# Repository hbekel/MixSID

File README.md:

# MixSID
*flexible Stereo-SID-board with integrated channel mixer*

The MixSID is a stereo SID board for the C64 that can be used with any combination 
of SID models on a wide range of C64 mainboards.

Features include an integrated stereo channel mixer, 
pragmatic stereo addressing scheme, flexible handling of io areas,
onboard audio input, output and digiboost circuits, 
dedicated stereo output, full paddle compatibility and versatile digital control.

For more information, please see the project page, available in both 
[english](http://www.henning-bekel.de/mixsid) and [german](http://www.henning-bekel.de/mixsid/de).

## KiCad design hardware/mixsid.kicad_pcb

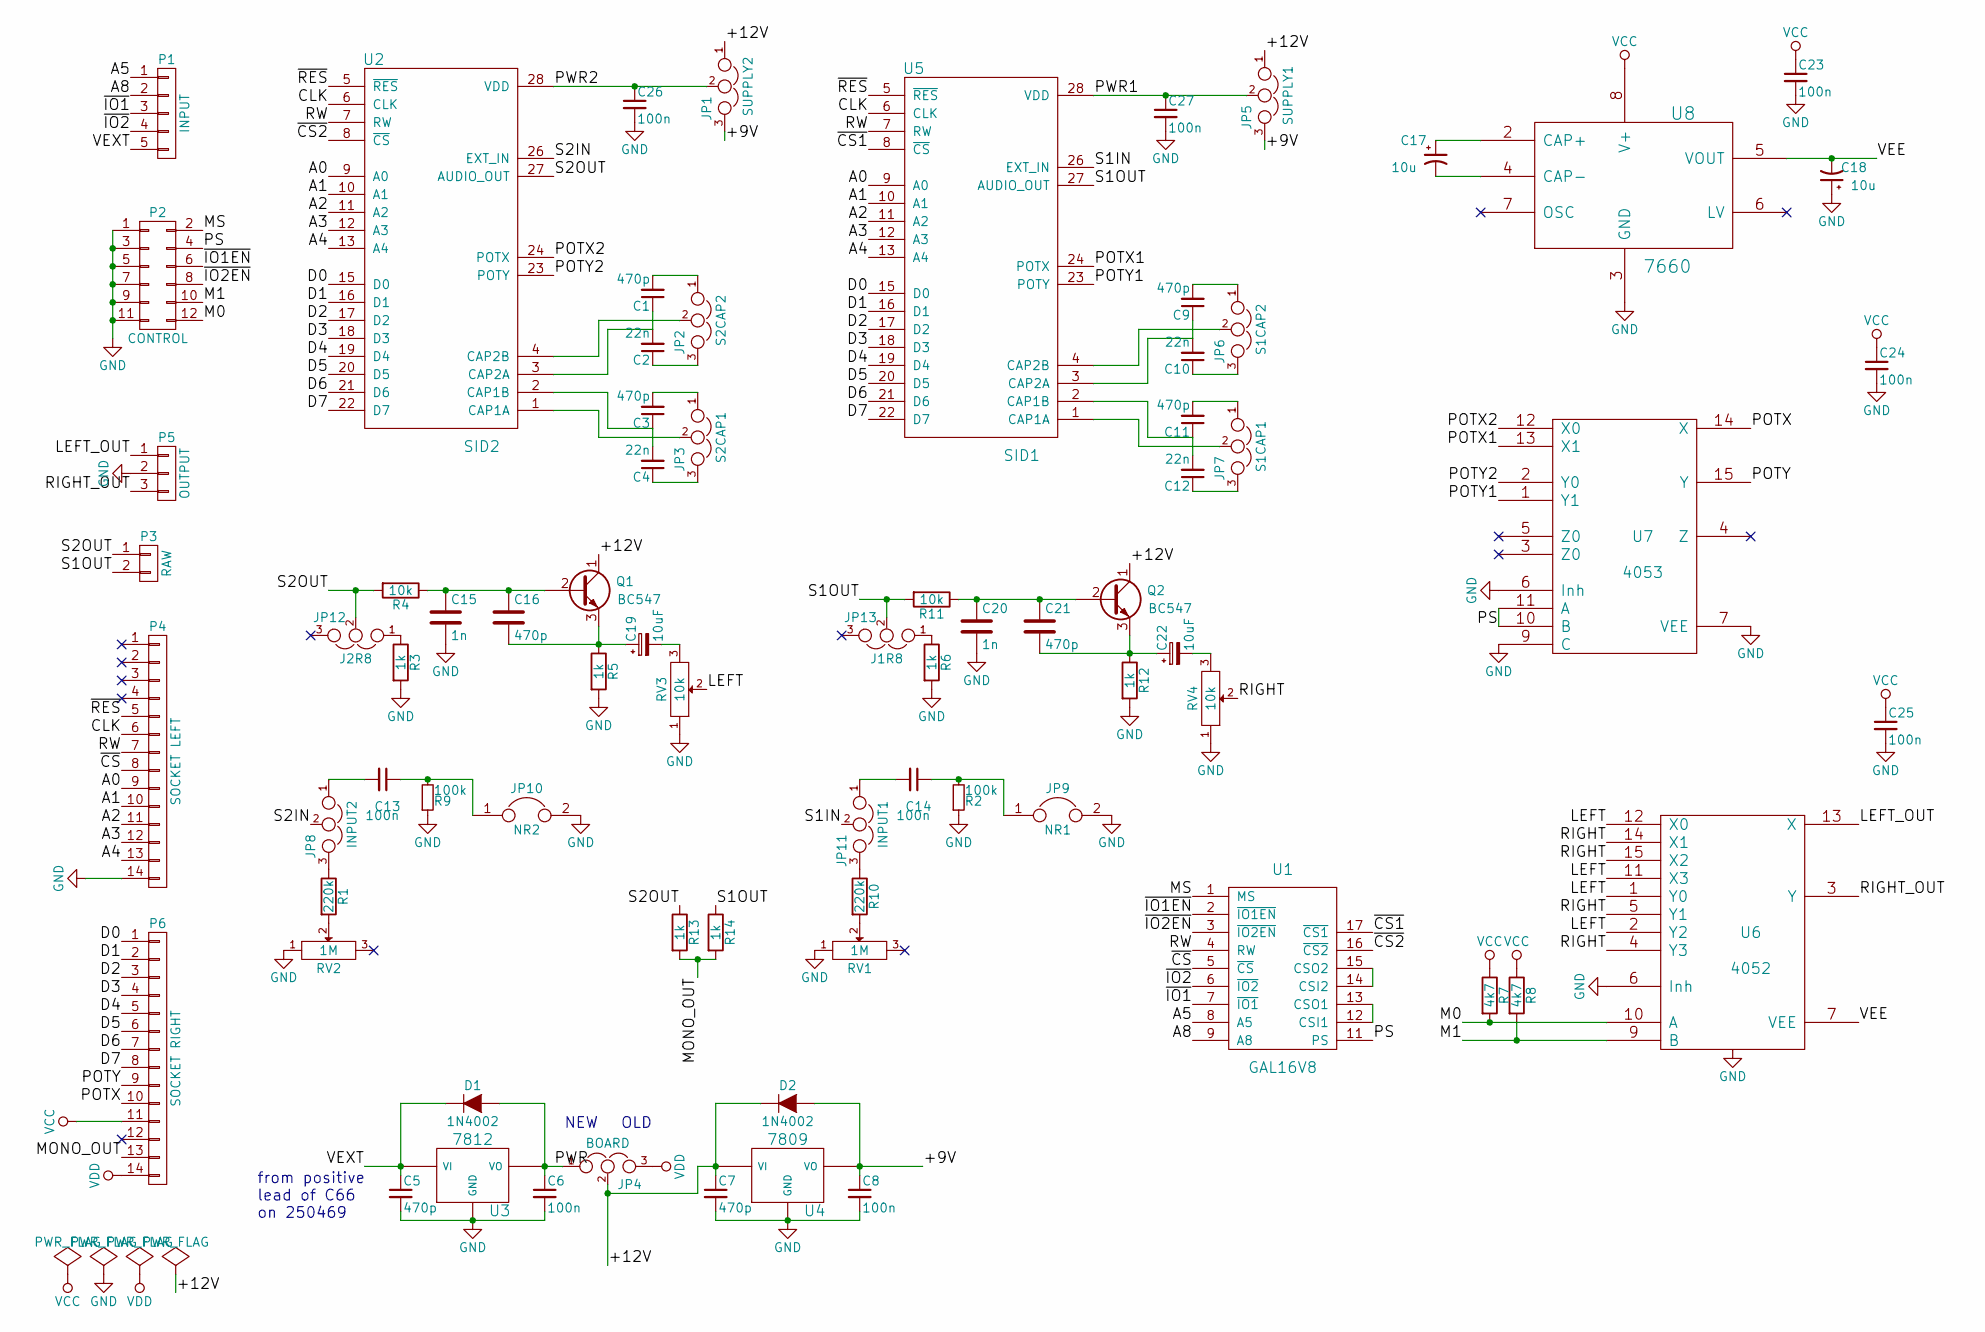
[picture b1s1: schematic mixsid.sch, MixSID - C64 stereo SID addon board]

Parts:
C1, C3, C5, C7, C9, C11, C16, C21: 470p; C_Disc_D3_P2.5
C2, C4, C10, C12: 22n; C_Disc_D3_P2.5
C6, C8, C13, C14, C23, C24, C25, C26, C27: 100n; C_Disc_D3_P2.5
C15, C20: 1n; C_Disc_D3_P2.5
C17, C18: 10u; C_Radial_D5_L6_P2.5
C19, C22: 10uF; C_Radial_D5_L6_P2.5
D1, D2: 1N4002; DO-41
JP1: SUPPLY2; Pin_Header_Straight_1x03_Pitch2.00mm
JP2: S2CAP2; Pin_Header_Straight_1x03_Pitch2.00mm
JP3: S2CAP1; Pin_Header_Straight_1x03_Pitch2.00mm
JP4: BOARD; Pin_Header_Straight_1x03
JP5: SUPPLY1; Pin_Header_Straight_1x03_Pitch2.00mm
JP6: S1CAP2; Pin_Header_Straight_1x03_Pitch2.00mm
JP7: S1CAP1; Pin_Header_Straight_1x03_Pitch2.00mm
JP8: INPUT2; Pin_Header_Straight_1x03_Pitch2.00mm
JP9: NR1; Pin_Header_Straight_1x02
JP10: NR2; Pin_Header_Straight_1x02
JP11: INPUT1; Pin_Header_Straight_1x03_Pitch2.00mm
JP12: J2R8; Pin_Header_Straight_1x03_Pitch2.00mm
JP13: J1R8; Pin_Header_Straight_1x03_Pitch2.00mm
P1: INPUT; Pin_Header_Straight_1x05
P2: CONTROL; Pin_Header_Straight_2x06
P3: RAW; Pin_Header_Straight_1x02
P4: SOCKET LEFT; Pin_Header_Straight_1x14
P5: OUTPUT; Pin_Header_Straight_1x03
P6: SOCKET RIGHT; Pin_Header_Straight_1x14
Q1, Q2: BC547; TO-92_Inline_Narrow_Oval
R1, R10: 220k; R1
R2, R9: 100k; R1
R3, R5, R6, R12, R13, R14: 1k; R1
R4, R11: 10k; R1
R7, R8: 4k7; R1
RV1, RV2: 1M; Potentiometer_Bourns_3296W_3-8Zoll_Inline_ScrewUp
RV3, RV4: 10k; Potentiometer_Bourns_3339P_Angular_ScrewUp
U1: GAL16V8; DIP-20_W7.62mm
U2: SID2; DIP-28_W15.24mm
U3: 7812; TO-220
U4: 7809; TO-220
U5: SID1; DIP-28_W15.24mm
U6: 4052; DIP-16_W7.62mm
U7: 4053; DIP-16_W7.62mm
U8: 7660; DIP-8_W7.62mm

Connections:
/+9V: C8.1, D2.2 (A), JP1.3, JP5.3, U4.3 (VO)
/+12V: C7.1, D2.1 (K), JP1.1, JP4.2, JP5.1, Q1.1 (C), Q2.1 (C), U4.1 (VI)
/A0: P4.9, U2.9 (A0), U5.9 (A0)
/A1: P4.10, U2.10 (A1), U5.10 (A1)
/A2: P4.11, U2.11 (A2), U5.11 (A2)
/A3: P4.12, U2.12 (A3), U5.12 (A3)
/A4: P4.13, U2.13 (A4), U5.13 (A4)
/A5: P1.1, U1.8 (A5)
/A8: P1.2, U1.9 (A8)
/CLK: P4.6, U2.6 (CLK), U5.6 (CLK)
/D0: P6.1, U2.15 (D0), U5.15 (D0)
/D1: P6.2, U2.16 (D1), U5.16 (D1)
/D2: P6.3, U2.17 (D2), U5.17 (D2)
/D3: P6.4, U2.18 (D3), U5.18 (D3)
/D4: P6.5, U2.19 (D4), U5.19 (D4)
/D5: P6.6, U2.20 (D5), U5.20 (D5)
/D6: P6.7, U2.21 (D6), U5.21 (D6)
/D7: P6.8, U2.22 (D7), U5.22 (D7)
/LEFT: RV3.2, U6.1 (Y0), U6.2 (Y2), U6.11 (X3), U6.12 (X0)
/LEFT_OUT: P5.1, U6.13 (X)
/M0: P2.12, R7.2, U6.10 (A)
/M1: P2.10, R8.2, U6.9 (B)
/MONO_OUT: P6.13, R13.2, R14.2
/MS: P2.2, U1.1 (MS)
/POTX: P6.10, U7.14 (X)
/POTX1: U5.24 (POTX), U7.13 (X1)
/POTX2: U2.24 (POTX), U7.12 (X0)
/POTY: P6.9, U7.15 (Y)
/POTY1: U5.23 (POTY), U7.1 (Y1)
/POTY2: U2.23 (POTY), U7.2 (Y0)
/PS: P2.4, U1.11 (PS), U7.10 (B), U7.11 (A)
/PWR: C6.1, D1.2 (A), JP4.1, U3.3 (VO)
/PWR1: C27.1, JP5.2, U5.28 (VDD)
/PWR2: C26.1, JP1.2, U2.28 (VDD)
/RIGHT: RV4.2, U6.4 (Y3), U6.5 (Y1), U6.14 (X1), U6.15 (X2)
/RIGHT_OUT: P5.3, U6.3 (Y)
/RW: P4.7, U1.4 (RW), U2.7 (RW), U5.7 (RW)
/S1IN: JP11.2, U5.26 (EXT_IN)
/S1OUT: JP13.2, P3.2, R11.2, R14.1, U5.27 (AUDIO_OUT)
/S2IN: JP8.2, U2.26 (EXT_IN)
/S2OUT: JP12.2, P3.1, R4.2, R13.1, U2.27 (AUDIO_OUT)
/VEE: C18.2, U6.7 (VEE), U8.5 (VOUT)
/VEXT: C5.1, D1.1 (K), P1.5, U3.1 (VI)
/~CS: P4.8, U1.5 (~CS)
/~CS1: U1.17 (~CS1), U5.8 (~CS)
/~CS2: U1.16 (~CS2), U2.8 (~CS)
/~IO1: P1.3, U1.7 (~IO1)
/~IO1EN: P2.6, U1.2 (~IO1EN)
/~IO2: P1.4, U1.6 (~IO2)
/~IO2EN: P2.8, U1.3 (~IO2EN)
/~RES: P4.5, U2.5 (~RES), U5.5 (~RES)
GND: C5.2, C6.2, C7.2, C8.2, C15.2, C18.1, C20.2, C23.2, C24.2, C25.2, C26.2, C27.2, JP9.2, JP10.2, P2.1, P2.3, P2.5, P2.7, P2.9, P2.11, P4.14, P5.2, R2.1, R3.2, R5.2, R6.2, R9.1, R12.2, RV1.1, RV2.1, RV3.1, RV4.1, U1.10 (GND), U2.14 (GND), U3.2 (GND), U4.2 (GND), U5.14 (GND), U6.6 (Inh), U6.8 (VSS), U7.6 (Inh), U7.7 (VEE), U7.8 (GND), U7.9 (C), U8.3 (GND)
unnamed: C1.1, C2.2, U2.3 (CAP2A)
unnamed: C1.2, JP2.1
unnamed: C2.1, JP2.3
unnamed: C3.1, C4.2, U2.2 (CAP1B)
unnamed: C3.2, JP3.1
unnamed: C4.1, JP3.3
unnamed: C9.2, JP6.1
unnamed: C10.1, JP6.3
unnamed: C9.1, C10.2, U5.3 (CAP2A)
unnamed: C11.1, C12.2, U5.2 (CAP1B)
unnamed: C11.2, JP7.1
unnamed: C12.1, JP7.3
unnamed: C13.1, JP10.1, R9.2
unnamed: C13.2, JP8.1
unnamed: C14.1, JP9.1, R2.2
unnamed: C14.2, JP11.1
unnamed: C15.1, C16.1, Q1.2 (B), R4.1
unnamed: C16.2, C19.1, Q1.3 (E), R5.1
unnamed: C17.1, U8.2 (CAP+)
unnamed: C17.2, U8.4 (CAP-)
unnamed: C19.2, RV3.3
unnamed: C20.1, C21.1, Q2.2 (B), R11.1
unnamed: C21.2, C22.1, Q2.3 (E), R12.1
unnamed: C22.2, RV4.3
unnamed: JP2.2, U2.4 (CAP2B)
unnamed: JP3.2, U2.1 (CAP1A)
unnamed: JP6.2, U5.4 (CAP2B)
unnamed: JP7.2, U5.1 (CAP1A)
unnamed: JP8.3, R1.1
unnamed: JP11.3, R10.1
unnamed: JP12.1, R3.1
unnamed: JP13.1, R6.1
unnamed: R1.2, RV2.2
unnamed: R10.2, RV1.2
unnamed: U1.12 (CSI1), U1.13 (CSO1)
unnamed: U1.14 (CSI2), U1.15 (CSO2)
VCC: C23.1, C24.1, C25.1, P6.11, R7.1, R8.1, U1.20 (VCC), U2.25 (VCC), U5.25 (VCC), U6.16 (VCC), U7.16 (VCC), U8.8 (V+)
VDD: JP4.3, P6.14

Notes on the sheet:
NEW
OLD
from positive lead of C66 on 250469

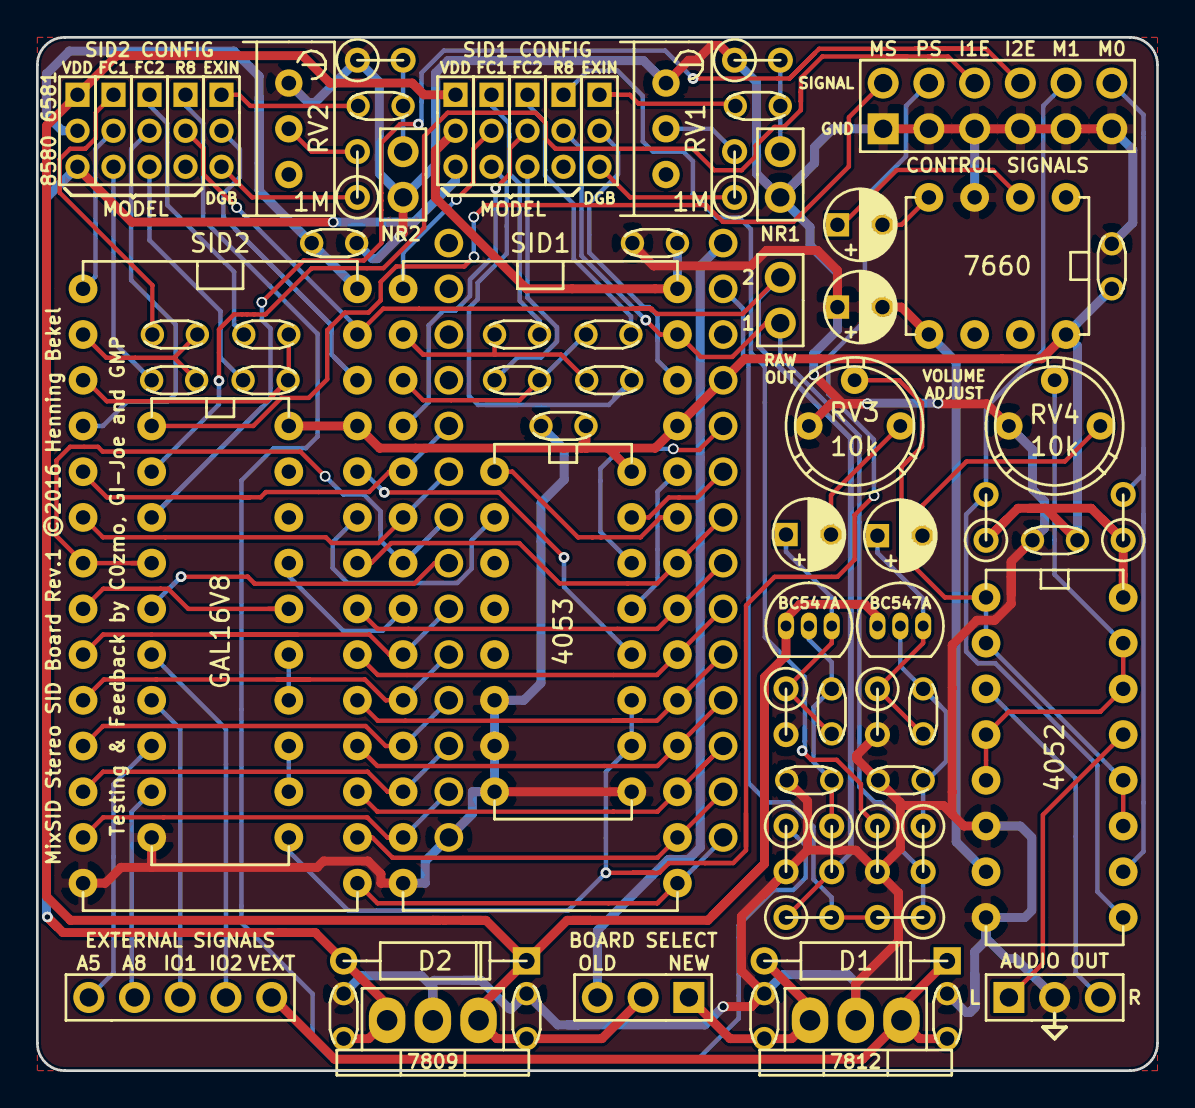
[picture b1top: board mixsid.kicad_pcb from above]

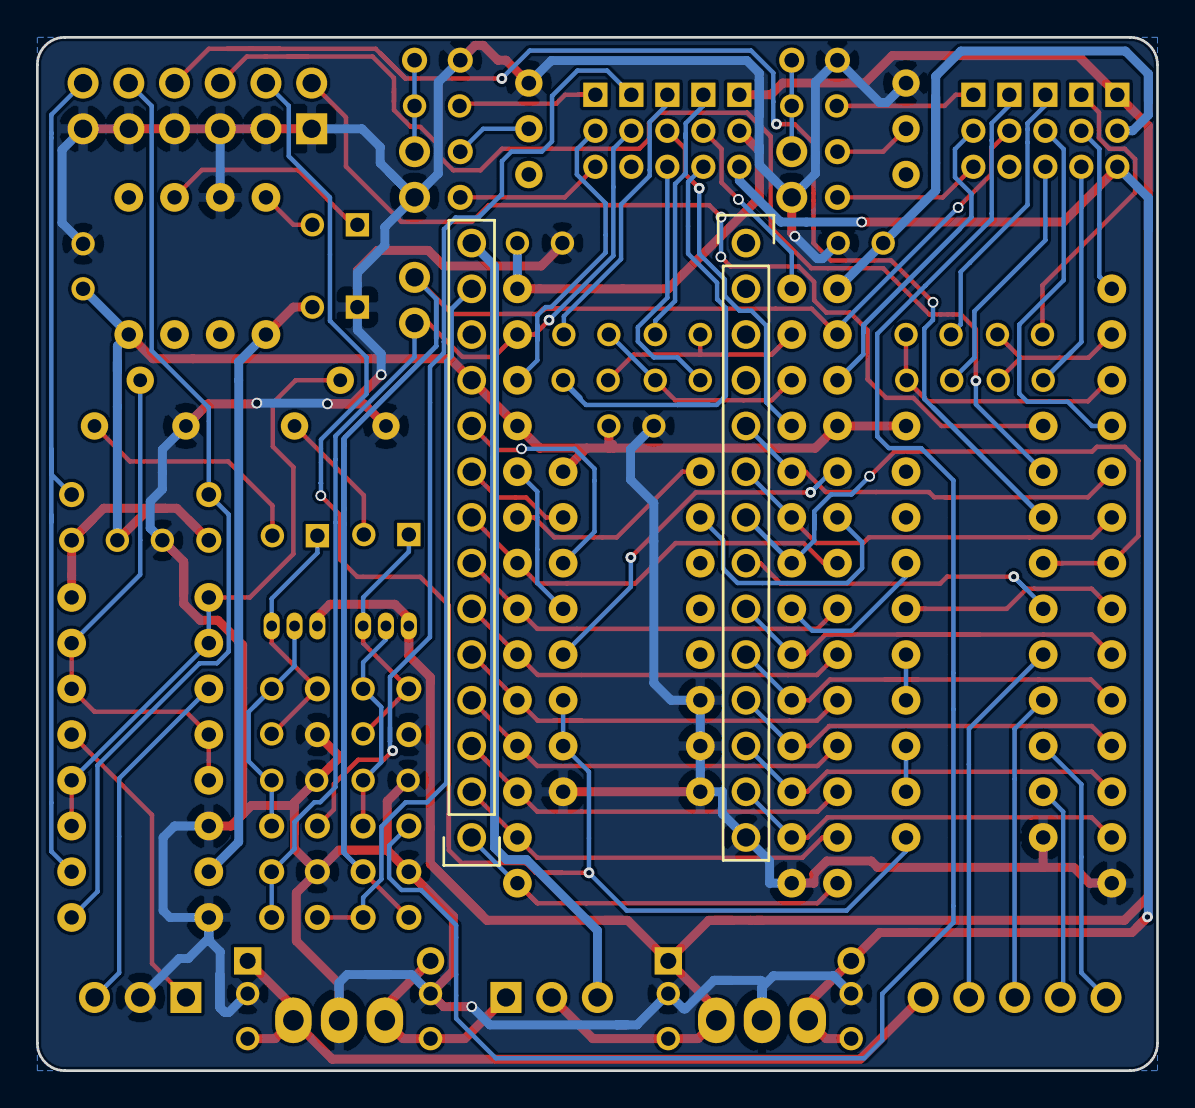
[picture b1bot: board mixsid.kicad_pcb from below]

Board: 2 copper layers, 62.2 x 57.4 mm, 76 parts (2 on the bottom side), 90 nets.

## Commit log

2016-03-01 Initial commit, first draft of GAL logic and rationale
2016-03-02 Added priority select logic, added more documentation/thoughts
2016-03-03 Added IO enable/disable logic, improved proposal text
2016-03-03 Added hardware and firmware folders, added empty kicad project
2016-03-03 Hardware: First rough draft of schematics and pcb placement
2016-03-04 Hardware: Added mixing and simple opamp output circuit
2016-03-04 Hardware: Added notes about where to get +16v on 250469
2016-03-07 Hardware: Added optional digifix circuits for both chips
2016-03-07 Hardware/Firmware: Supply separate IO enable lines (IO1EN, IO2EN)
2016-03-07 Hardware: Removed digifix circuits, added 7660, mix after opamps
    The 4052 can only mix signals within 2-8V and VCC must be <10V. Therefore
    the amplified output must be mixed.
2016-03-09 Hardware: Rearranged components, first successful (auto)routing
2016-03-09 Hardware: Added some proper pinheaders, new routing, added more docs
2016-03-09 Hardware: Added pullups for M0 and M1, rerouted
2016-03-10 Hardware: Improved routing, changed opamp from TL072 to OPA132
2016-03-11 Hardware: Added digifix again, rearranged components, rerouted
2016-03-12 Hardware: Fixed POTX/POTY connected to SID2
2016-03-14 Hardware: Now using original output circuits instead of opamp
2016-03-15 Hardware: Use pin headers instead of dip socket for the sid socket
2016-03-17 Hardware: Rearranged components, made control lines usable with jumpers
2016-03-19 Hardware: Added optional mono mixing into existing output circuit
2016-03-19 Hardware: Rearranged components below sids to fit between sockets
2016-03-21 Firmware: Fixed addressing for CS1 and IO1/IO2
    CS1 is only asserted if both A5 and A8 are low, IO1/IO2 must take effect
    regardless of CS.
2016-03-21 Hardware: Fixed transistor symbols/footprints and extin jumper positions
2016-03-21 Hardware: Fixed wrong SID socket placement (mirrored), improved routing
2016-03-21 Hardware: Cleaned up silkscreen, added markings, improved routing
2016-03-21 Hardware: Corrected filter capacitor values for 6581 (470p)
2016-03-22 Hardware: Improved silkscreen, corrected pot refs
2016-03-22 Hardware: Improved silkscreen, added warning labels on board jumper
2016-03-22 Hardware: Improved silkscreen, plotted gerber files
2016-04-08 Hardware: Fixed decoupling caps (now polarized), removed gerbers
2016-04-11 Hardware: Fixed orientation of VEE decoupling caps on silkscreen
2016-04-11 Hardware: Fixed values of digifix safety resistors (220k instead of 200)
2016-04-11 Hardware: Silkscreen cleanup
2016-04-11 Hardware: Adjusted regulator bypass cap values to 470p
2016-04-11 Hardware: Reordered filter caps for SID2 (consistency)
2016-04-11 Hardware: Removed SID2 pot connector, moved board select jumper
2016-04-11 Hardware: Renamed +16V line to VEXT, improved silk screen
2016-04-11 Hardware: Corrected order of SIDs on audio channels, default mix setting
    Now the left sid appears on the left channel and the right sid on the right
    channel. Also the default mix state (without driving M0 and M1) has been
    changed to Left/Right. This should match expectations.
2016-04-11 Hardware: Removed priority select, rearranged GAL pin layout
    Switching SID priorities does not seem very useful and will break paddles
    when priority is swapped in stereo addressing mode.
2016-04-11 Hardware: Improved routing, silkscreen
2016-04-11 Hardware: Improved routing, copper pours
2016-04-12 Hardware: Improved routing and silkscreen
2016-04-12 Hardware: Flipped VEE bypass cap allowing less ambigious silkscreen
2016-04-13 Hardware: Rearranged components to increase top clearance, rerouted
2016-04-14 Hardware: Added explicit ground path from power supply to signal ground
2016-04-14 Hardware: Improved routing
2016-04-14 Hardware: Cleaned up silkscreen
2016-04-14 Hardware: Improved silkscreen
2016-04-14 Project renamed to MixSID
2016-04-14 Documentation: Improved and clarified addressing, firmware description
2016-04-14 Firmware: Adjusted firmware tag to new project name
2016-04-14 Hardware: Improved routing, decreased pin header pads for SID socket
2016-04-15 Hardware: Improved routing, placement of 7812 and caps, silkscreen
2016-04-15 Hardware: Improved routing of GND and VEXT around voltage regulators
2016-04-15 Hardware: Added gerber files for second prototype
2016-04-20 Hardware: Removed gerber files during development
2016-04-26 Hardware: Added voltage dividers for optional volume adjustments
2016-04-26 Hardware: Changed 7660 caps to small electrolytics, improved silkscreen
2016-04-27 Hardware: Improved routing, scaled caps 3d models to size, improved 3d view
2016-04-28 Hardware: Moved bottom connectors slightly up to save some more space
2016-04-28 Hardware: Priority, paddle multiplexing, volume adjust, bigger board size
    Priority select has been reimplemented, allowing to virtually swap sids in
    terms of addressing (which SID stays at home and which one goes stereo).
    A 4053 multiplexer has been added to keep the paddles working regardless of
    priority. Paddle lines are always routed to the SID currently at $d400.
    Two pots have been added to allow volume adjustments before mixing in order
    to adjust two different models in overall volume (6581 are usually louder).
2016-04-29 Hardware: Replaced balance pots with round types (bourns 3339), rearranged
2016-04-29 Firmware/Hardware: RW2 signal controls SID2 RW during parallel addressing
    Depending on RW2, SID2 is write-only or read-write when addressed alongside
    SID1.
    The default setting is write-only to assure proper paddle support.
    For mono tunes that use the readable registers for special effects,
    parallel addressing would result in only one SID playing those effects
    properly, thus RW2 allows the user to make both sids read-write.
2016-04-30 Hardware: Use round pots fot digifix as well
2016-05-01 Hardware: Rerouting in progress...
2016-05-02 Hardware: Use rect pots for digifix again, placed volume pods horizontally
2016-05-03 Hardware: Improved routing, silkscreen and rendering
2016-05-03 Documentation: Improved addressing document, added PS & RW2 descriptions
2016-05-04 Hardware: Added raw audio out terminal, improved routing
2016-05-04 Revert "Hardware: Added raw audio out terminal, improved routing"
    This reverts commit 8f31b2ae4ef6d7f69e92e6d42a67aa70f75f1e9c.
2016-05-04 Hardware: Swapped MS/PS, improved routing, silkscreen
2016-05-04 Hardware: Prototype 3: Added gerber files for production
2016-05-04 Documentation: Improved addressing description
2016-05-11 Hardware: Fixed connection and orientation of volume pots
2016-05-11 Hardware: Added pin header to access raw audio out as well
2016-05-11 Hardware: Improved thermal release at ground connections
2016-05-11 Hardware: Added -5V test point, improved silkscreen
2016-05-13 Hardware: Improved component placement, cap orientation for 7660
2016-05-16 Documentation: Added output circuit simulation (falstad)
2016-05-17 Hardware: Added R8 Jumpers, Feed SID specific VDD into output stages
2016-05-18 Hardware: Reverted to +12V for both output stages, rerouted, refined
2016-05-20 Hardware: Changed orientation of 7660 caps
    Provide common orientation for all polarized caps on the board.
2016-05-20 Hardware: Improved silkscreen of resistor footprints
2016-05-23 Hardware: Added bypass caps at SID VDD supplies
2016-05-23 Hardware: Added protection diodes to regulators, board height increased
2016-05-23 Documentation: Improved output circuit simulation
2016-05-24 Hardware: Improved thermal relief at GND pads
2016-05-24 Hardware: Rounded pcb corners added
2016-05-24 Production: Removed previous gerber files
2016-05-24 Production: Added gerber files for prototype revision 4
2016-05-25 Hardware: Improved 3d view, added jumpers
2016-05-25 Hardware: Added footprints for 2mm headers with and without jumpers
2016-06-01 Hardware: Improved 3d view, added short legged TO-220 model
2016-06-02 Firmware: Only allow parallel reads when A0 xnor A1, obsoletes RW2
    This prevents read access in parallel addressing mode only for POTX and
    POTY ($19, $1A) while still allowing them for OSC3 and ENV3 ($1B, $1C).
    Thus paddles AND effects based on OSC3/ENV3 will simply work any time,
    regardless of addressing mode and priority.
2016-06-02 Hardware: Adjusted schematics, removed RW2 from board, rerouted
2016-06-02 Hardware: Improved component placement, Firmware: updated description
2016-06-10 Hardware/Firmware: Removed selective write-only logic again, not required
    The previously added logic for keeping only the POTX and POTY lines
    write-only has proven unneccessary and has thus been reverted. Now all
    readable registers are disabled for the secondary SID in parallel mode
    again. The previously introduced RW2 signal is still unneccessary. Both
    paddles and OSC3/ENV3 effects work well in parallel mode after all.
2016-06-10 Documentation: updated to reflect recent changes (mostly RW2 removal)
2016-06-14 Hardware: Removed resistor models from mainboard audio out mixing slots
2016-06-21 Hardware: Added sockets to 3D model
2016-06-27 Hardware: Updated schematic/pcb metadata
2016-06-28 Hardware: Added makefile to rename and zip gerber files
2016-06-28 Hardware: Added gerber files for Revision 1
2016-07-18 Project: Added Readme.md for github
2016-07-18 Project: Added Makefile, finishing touches, preparing release
2016-07-18 Version 1.0
2016-10-16 Hardware: Small hack for the C128 to enable 2nd SID at $D500 in C64 mode
    Added documentation for a small hardware hack for the C128 that
    makes the secondary SID also appear at $D500 in C64 mode for
    stereo addressing.
    This hack should work for other stereo SID solutions as well.
    See firmware/c128/README for details and instructions.
2016-12-20 Makefiles: Improved Makefile for renaming/zipping gerber files
2017-02-23 Project: Improved .gitignore file

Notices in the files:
hardware/mixsid.kicad_pcb:
MixSID Stereo SID Board Rev.1 ©2016 Henning Bekel
